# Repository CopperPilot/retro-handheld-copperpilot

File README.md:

# CopperPilot Retro Handheld: 4-Layer ESP32-S3 Handheld Console Hardware

The CopperPilot Retro Handheld is an ultra-compact, single-board retro handheld console design built on a 4-layer FR-4 PCB (**63.00 mm x 80.00 mm**) with a parametric snap-fit enclosure. Built around an Espressif ESP32-S3 dual-core microcontroller, the hardware features a 2.4-inch 320x240 ILI9341 SPI color TFT display, 14 responsive gameplay and shoulder pushbuttons, integrated USB-C charging and native USB-OTG/JTAG programming, automatic load-sharing battery power management for uninterrupted gameplay while charging, and a removable 1000 mAh Li-Po cell.

> **Project status:** this repository contains the hardware (schematic, PCB, enclosure CAD, and manufacturing outputs) only. There is **no firmware yet**, so no frame rates, emulator compatibility, or battery runtime have been measured on this board.

---

## 3D Enclosure & Industrial Design Showcase

### 3D CAD Enclosure Renders

| Front Face & Controls | Rear Shell & Grip Channels |
| :---: | :---: |
|  |  |
| **Front bezel, display window & keycaps** | **Rear grooved shell & battery hatch** |

| 3/4 Isometric View | Exploded Subsystem Assembly |
| :---: | :---: |
|  |  |
| **Assembled enclosure** | **Front Bezel, PCBA, Floating Keycaps, Rear Shell & Door** |

### Complete 3D Assembly Motion Animation (GIF & MP4)

<p align="center">
  
  <br>
  <em>Sequential 3D Assembly Animation: PCBA SMT/TH Component Populating &rarr; Gamepad Keycaps Seating over Tactile Switches &rarr; 2.4" Display Panel Seating &amp; FPC Interconnect into J3 &rarr; Front Bezel Lowering over Controls &amp; Alignment Pins &rarr; Li-Po Battery Seating into Rear Cavity &rarr; Rear Grooved Shell Closing &amp; Flush Snap Mating &rarr; 360&deg; Watertight Turntable Inspection</em>
  <br>
  <strong>High-definition MP4 video asset:</strong> <code>docs/images/case_assembly_video.mp4</code>
</p>

---

## 4-Layer Routed PCB Layout & Schematic Capture

| Front Layer (`F.Cu` — Tactile Controls & Display) | Back Layer (`B.Cu` — ESP32-S3, USB-C & Power ICs) |
| :---: | :---: |
|  |  |

### Photorealistic 3D KiCad PCB Renders (`kicad-cli pcb render`)

| KiCad 3D Top View (Tactile Controls, JST-GH J3 & Top Shoulder Switches) | KiCad 3D Bottom View (ESP32-S3 Module, USB-C, JST-PH & Power Management) |
| :---: | :---: |
|  |  |
| *Populated Front: 14x Tactile Switches, J3 Display Receptacle, D1/D3 LEDs* | *Populated Back: ESP32-S3-WROOM-1, USB-C, JST-PH Battery Header, LDO & Charger* |

<p align="center">
  
  <br>
  <em>Complete 6-Block Schematic Capture (USB-C Power, Li-Po Charger, Load Sharing, ESP32-S3 Core, ILI9341 TFT & 14 Pushbuttons)</em>
</p>

---

## System Architecture

```
                    +-------------------------------------------------------+
                    |                   Power Subsystem                     |
                    | USB-C (J1) ---> USBLC6-2SC6 (U1) ESD Protection       |
                    |                 |                                     |
                    |                 +---> MCP73831 (U2) Charger (500mA)   |
                    |                 |     |                               |
                    |                 |     v                               |
                    |                 |    JST-PH 1S LiPo (J2)              |
                    |                 |     |                               |
                    |                 v     v                               |
                    |           AO3401A (Q1) + MBR0520 (D2) Power Path      |
                    |                       | (Auto Load-Sharing)           |
                    |                       v                               |
                    |              Main Power Switch (SW1)                  |
                    |                       |                               |
                    |                       +---> 100k/100k Divider (IO1)   |
                    |                       v                               |
                    |              AP2112K-3.3 (U3) 600mA LDO               |
                    +-----------------------|-------------------------------+
                                            | +3.3V System Rail
+--------------------------+  Hardware FSPI +-------------------------------+
|  2.4" 320x240 ILI9341    |<---------------|       ESP32-S3-WROOM-1        |
|  SPI Color TFT (J3)      |  SCK, MOSI,    |  Dual-Core Xtensa LX7 240MHz  |
|  2N7002 Backlight Driver |<---------------|  512KB SRAM, 8MB Flash        |
+--------------------------+  CS, DC, RST,  |  2MB PSRAM, Wi-Fi 4 / BLE 5.0 |
                              PWM Backlight +---+---+---+---+---+---+---+---+
                                                |   |   |   |   |   |   |
     14x Active-Low Tactile Pushbuttons:        |   |   |   |   |   |   |
     D-Pad (Up, Down, Left, Right) <------------+   |   |   |   |   |   |
     Action Diamond (A, B, X, Y) <------------------+   |   |   |   |   |
     Utility Controls (Select, Start) <-----------------+   |   |   |   |
     Shoulder Triggers (L1, L2, R1, R2) <-------------------+   |   |   |
     Boot & Reset Service Switches (SW2, SW3) <-----------------+---+---+
```

---

## Hardware Specifications & Computational Capability

- **Chassis & Form Factor**: 63.00 mm x 80.00 mm ultra-compact 4-layer FR-4 PCB with R=2.50 mm corner radii, 4 precision 2.20 mm alignment holes (`H1`–`H4`), and 4 through-PCB snap-hook retention notches (`SL1`, `SL2`, `SR1`, `SR2`).
- **Core Processing Unit**: Espressif ESP32-S3-WROOM-1-N8R2 (dual-core 32-bit Xtensa LX7 @ 240 MHz, 512 KB internal SRAM, 8 MB Quad-SPI Flash, 2 MB Quad-SPI PSRAM, 2.4 GHz 802.11 b/g/n Wi-Fi + Bluetooth 5.0 LE).
  - **Game & Emulator Capability (not yet verified on this board)**: There is no firmware for this board yet, so no frame rates or emulator results are claimed here. The figures below are design-level estimates and third-party reports from other ESP32-S3 hardware, cited for reference only:
    - Display link: the ESP32-S3 SPI2 (FSPI) peripheral supports DMA transfers. A full 320x240 RGB565 frame is 150 KB (300 KB double-buffered, well within the 2 MB PSRAM). Achievable frame rate depends on the SPI clock the ILI9341 panel and cabling sustain in practice (commonly 40 MHz). The [esp-box-emu](https://github.com/esp-cpp/esp-box-emu) project reports a "~31 fps ceiling" for 320x240x16bpp output on its ESP32-S3 panel.
    - Emulators on other ESP32-S3 devices: [esp-box-emu](https://github.com/esp-cpp/esp-box-emu) runs NES (nofrendo), Game Boy / Game Boy Color (gnuboy), Sega Master System / Game Gear, Genesis and Doom on the ESP32-S3-BOX. [Retro-Go](https://github.com/ducalex/retro-go) supports NES, Game Boy / Color, Master System, Game Gear, PC Engine and more on ESP32 handhelds, with ESP32-S3 community ports. [PaperBoy S3](https://www.tomshardware.com/video-games/retro-gaming/designer-turns-niche-e-ink-dev-board-into-a-60hz-game-boy-handheld-960x540-display-powered-by-ultra-low-cost-esp32-s3-microcontroller) (Tom's Hardware) runs a Game Boy emulator on an ESP32-S3, with the chip fully loaded.
    - These results come from different hardware and firmware. Performance on this board has to be measured once firmware exists.
    - *Audio note*: The board does not integrate an analog audio amplifier or speaker. Audio is supported wirelessly via Bluetooth 5.0 LE / A2DP or via external PWM buzzer on spare GPIO.
- **Display Subsystem & Connector `J3`**:
  - **Board-Mounted SMT Socket (`J3`)**: JST Sales America `SM10B-GHS-TB(LF)(SN)` (10-position 1.25 mm pitch horizontal SMD header with solder retention tabs).
  - **Turnkey Sourced Display Module (`DISP1`)**: **Waveshare 15933** (MPN: `15933` / DigiKey: `2649-15933-ND` / LCSC: `C2913222`) or EastRising `ER-TFT024-3`.
    - 2.4-inch 320x240 RGB TFT LCD, Sitronix/Ilitek ILI9341 4-wire SPI controller, 3.3V DC logic, active area 48.96 x 36.72 mm, 10-conductor cable harness with mating plug JST `GHR-10V-S`.
  - Onboard 2N7002 N-channel MOSFET backlight switch (`Q2`) with 10 Ω ballast resistor (`R14`) and 100 kHz PWM brightness dimming on GPIO21.
- **Power Management & Dynamic Load-Sharing**:
  - Microchip MCP73831T-2ACI/OT linear Li-Po/Li-Ion charge management controller configured for 500 mA fast charge (`R_PROG` = 2.0 kΩ 1%).
  - Automatic dynamic load sharing via AO3401A P-channel MOSFET (`Q1`, $R_{DS(on)} < 50\text{ m}\Omega$) and MBR0520 Schottky barrier diode (`D2`, $V_F = 0.38\text{ V}$). When 5V USB-C is plugged in, the system runs directly off USB power while the battery charges undisturbed at its full C-rate; upon disconnect, the MOSFET transparently switches system load back to battery without voltage droop.
  - Diodes Inc. AP2112K-3.3 ultra-low-dropout 600 mA CMOS regulator with 250 mV dropout voltage, powering the console reliably down to 3.55 V battery cutoff.
  - Precision 100 kΩ / 100 kΩ 1% resistor divider (`R8`, `R9`) with 100 nF smoothing capacitor (`C6`) on ESP32-S3 `ADC1_CH0` (GPIO1) for fuel gauge battery telemetry.
  - Estimated system consumption (design estimate, not measured): ~220 mA @ 3.3V (~0.73W) with display backlight at 100% and CPU at 240 MHz, which would give roughly 4.5 hours from a 1000 mAh Li-Po cell.
- **Controls & Non-Colliding 3D Keycaps**:
  - 14 front-mounted tactile switches with 10 kΩ pull-up networks:
    - 4-way D-Pad (`UP`, `DOWN`, `LEFT`, `RIGHT`) centered at (14.65, 60.96 mm).
    - 4-button action diamond (`A`, `B`, `X`, `Y`) centered at (47.97, 61.75 mm).
    - 2 utility buttons (`SELECT`, `START`) centered at (31.24, 69.70 mm).
    - 4 shoulder triggers (`L1`, `L2`, `R1`, `R2`) centered at (9.50, 18.33, 53.50, 44.67 mm).
  - **Guaranteed Physical Clearances**:
    - D-Pad to Select button flange clearance: **1.49 mm** (zero collision).
    - ABXY adjacent button flange clearance: **>1.22 mm** between all neighboring pairs.
    - L1/L2 and R2/R1 shoulder trigger gap: **0.93 mm** inter-button clearance.
    - Keycap-to-bezel sliding clearance: **0.30 mm** radial clearance for friction-free actuation.

---

## Lion Circuits 4-Layer Manufacturing & PCBA Specifications

The hardware has been validated against Lion Circuits India turnkey PCBA design and procurement standards:

| Fabrication Parameter | Lion Circuits Standard Capability | Handheld Console Implementation | Design Margin |
| :--- | :--- | :--- | :--- |
| **Layer Count** | 4-Layer Multi-Layer FR-4 | **4 Layers** (`F.Cu`, `In1.Cu`, `In2.Cu`, `B.Cu`) | Standard |
| **Finished Thickness** | 1.6 mm nominal (+/- 10%) | **1.60 mm** | Exact Nominal |
| **Copper Weight** | 1.0 oz outer / 0.5 oz inner | **1.0 oz (35 µm) outer / 0.5 oz (17.5 µm) inner** | Standard |
| **Minimum Trace Width** | 6 mil (0.1524 mm) | **6 mil (0.1524 mm) min / 8 mil (0.20 mm) typ** | 100% Fab Compliant |
| **Minimum Trace Spacing** | 6 mil (0.1524 mm) | **6 mil (0.1524 mm) min / 8 mil (0.20 mm) typ** | 100% Fab Compliant |
| **Via Drill & Diameter** | 0.30 mm drill / 0.60 mm pad | **0.30 mm drill / 0.60 mm diameter** | Exact Standard Spec |
| **Annular Ring** | 6 mil (0.152 mm) minimum | **0.150 mm (6 mil)** | 100% Fab Compliant |
| **Copper to Board Edge** | 12 mil (0.30 mm) minimum | **0.40 mm (16 mil)** | +33% Safety Margin |
| **Surface Finish** | Lead-Free HASL or ENIG | **Electroless Nickel Immersion Gold (ENIG)** | Superior SMT Coplanarity |
| **Solder Mask & Silk** | Matte Black Mask / White Silk | **Matte Black / High-Contrast White** | Premium Aesthetic |

### Turnkey PCBA Bill of Materials (45 Verified Line Items)

| Item | Designators | Qty | Part / Value | Manufacturer | MPN | Package | Sourcing Channel |
| :---: | :--- | :---: | :--- | :--- | :--- | :--- | :--- |
| 1 | `U4` | 1 | Dual-Core MCU + PSRAM | Espressif Systems | `ESP32-S3-WROOM-1-N8R2` | SMD-41 (18x25.5mm) | DigiKey / Mouser / LCSC |
| 2 | `J1` | 1 | USB-C 2.0 16-Pin Receptacle | GCT / Hroparts | `USB4105-GF-A` / `TYPE-C-31-M-12` | USB-C-16P-TopMount | DigiKey / LCSC |
| 3 | `U1` | 1 | Rail-to-Rail ESD Diode Array | STMicroelectronics | `USBLC6-2SC6` | SOT-23-6 | DigiKey / Mouser |
| 4 | `U2` | 1 | 500mA Li-Po Charger | Microchip Technology | `MCP73831T-2ACI/OT` | SOT-23-5 | DigiKey / Mouser |
| 5 | `Q1` | 1 | P-MOSFET Load Sharing | Alpha & Omega Semi | `AO3401A` | SOT-23 | DigiKey / LCSC |
| 6 | `D2` | 1 | 20V 0.5A Schottky Diode | ON Semiconductor | `MBR0520LT1G` | SOD-123 | DigiKey / Mouser |
| 7 | `U3` | 1 | 600mA Ultra-Low-Dropout LDO | Diodes Incorporated | `AP2112K-3.3TRG1` | SOT-23-5 | DigiKey / Mouser |
| 8 | `Q2` | 1 | 60V 300mA N-MOSFET Backlight | Nexperia | `2N7002,215` | SOT-23 | DigiKey / Mouser |
| 9 | `D1` | 1 | Red LED (Charge Indicator) | Lite-On Inc. | `LTST-C190KRKT` | 0603 SMD | DigiKey / Mouser |
| 10 | `D3` | 1 | Green LED (Power Good) | Lite-On Inc. | `LTST-C190KGKT` | 0603 SMD | DigiKey / Mouser |
| 11 | `J2` | 1 | JST-PH 2-Pin Battery Header | JST Sales America | `S2B-PH-K-S(LF)(SN)` | JST_PH_1x02_P2.00mm | DigiKey / Mouser |
| 12 | `J3` | 1 | JST-GH 10-Pin Display Socket | JST Sales America | `SM10B-GHS-TB(LF)(SN)` | 10-Pin 1.25mm SMT | DigiKey / Mouser |
| 13 | `SW1` | 1 | SPDT Power Slide Switch | C&K / Hroparts | `PCM12SMTR` / `MSK-12C02` | SMT Slide Switch | DigiKey / LCSC |
| 14 | `SW4`-`SW11` | 8 | 6x6mm Tactile Switches | C&K Components | `PTS645SM43SMTR92 LFS` | 6.0x6.0mm SMD | DigiKey / Mouser |
| 15 | `SW12`,`SW13`,`SW2`,`SW3` | 4 | 6x3.5mm Tactile Switches | C&K Components | `PTS636 SM25 LFS` | 6.0x3.5mm SMD | DigiKey / Mouser |
| 16 | `SW14`-`SW17` | 4 | Ultra-Small Tactile Switches | Omron Electronics | `B3U-3000P` | 3.0x2.5mm SMD | DigiKey / Mouser |
| 17 | `DISP1` | 1 | 2.4" 320x240 ILI9341 SPI TFT | Waveshare / EastRising | `15933` / `ER-TFT024-3` | 2.4" Module + Cable | DigiKey / LCSC / Waveshare |
| 18 | `BT1` | 1 | 3.7V 1000mAh 1S Li-Po Cell | PKCELL / Adafruit | `LP803040` / `ID 258` | 40x30x8.0mm JST-PH | DigiKey / Adafruit |
| 19 | `CASE1` | 1 | CopperPilot Retro Handheld 3D Snap-Fit Case Kit | CopperPilot (in-house design) | `CP-RETRO-HANDHELD-CASE-V1` | 3D Watertight Enclosure | 3D Printed / Molded |
| 20-34 | `C1`-`C15` | 15 | Ceramic MLCC Decoupling | Yageo / Murata | 100nF, 1uF, 4.7uF, 10uF, 22uF | 0603 & 0805 | DigiKey / LCSC |
| 35-45 | `R1`-`R30` | 30 | Precision Chip Resistors | Yageo / Vishay | 10, 22, 1k, 2k 1%, 5.1k, 10k, 100k 1% | 0603 & 0805 | DigiKey / LCSC |

---

## Automated Verification Suite

The repository includes a **51-point automated PyTest hardware, assembly, and enclosure verification suite**:

```bash
$ make test
============================= test session starts ==============================
platform linux -- Python 3.13.9, pytest-9.1.1
collected 51 items

tests/test_assembly_e2e.py::TestEndToEndAssemblySequence::test_stage1_pcba_component_loading PASSED
tests/test_assembly_e2e.py::TestEndToEndAssemblySequence::test_stage2_kicad_3d_pcba_mesh_validation PASSED
tests/test_assembly_e2e.py::TestEndToEndAssemblySequence::test_stage3_buttons_clearance_and_zero_collision PASSED
tests/test_assembly_e2e.py::TestEndToEndAssemblySequence::test_stage4_buttons_seat_onto_pcba_zero_collision PASSED
tests/test_assembly_e2e.py::TestEndToEndAssemblySequence::test_stage5_buttons_seat_in_front_bezel_zero_collision PASSED
tests/test_assembly_e2e.py::TestEndToEndAssemblySequence::test_stage6_display_shelf_mating_and_j3_interconnect PASSED
tests/test_assembly_e2e.py::TestEndToEndAssemblySequence::test_stage7_pcba_mating_to_front_bezel_zero_collision PASSED
tests/test_assembly_e2e.py::TestEndToEndAssemblySequence::test_stage8_rear_shell_mating_over_pcb_zero_collision PASSED
tests/test_assembly_e2e.py::TestEndToEndAssemblySequence::test_stage9_battery_seating_and_rear_cavity_fit PASSED
tests/test_assembly_e2e.py::TestEndToEndAssemblySequence::test_stage10_continuous_kinematic_assembly_trajectories PASSED
tests/test_assembly_e2e.py::TestEndToEndAssemblySequence::test_stage11_full_console_assembly_envelope PASSED
tests/test_case.py::TestCaseFiles::test_stl_file_exists[case_front_bezel.stl] PASSED
tests/test_case.py::TestCaseFiles::test_stl_file_exists[case_rear_grooved.stl] PASSED
tests/test_case.py::TestCaseFiles::test_stl_file_exists[case_battery_door.stl] PASSED
tests/test_case.py::TestCaseFiles::test_stl_file_exists[buttons_dpad_abxy_sest_shoulders.stl] PASSED
tests/test_case.py::TestCaseFiles::test_stl_file_exists[copperpilot_retro_handheld_assembly.stl] PASSED
tests/test_case.py::TestCaseGeometry::test_front_bezel_envelope PASSED
tests/test_case.py::TestCaseGeometry::test_rear_shell_envelope PASSED
tests/test_case.py::TestCaseGeometry::test_battery_door_envelope PASSED
tests/test_case.py::TestCaseGeometry::test_mesh_manifolds_and_faces PASSED
tests/test_case.py::TestCaseGeometry::test_full_assembly_mesh PASSED
tests/test_case.py::TestCaseClearancesAndCollisions::test_all_buttons_zero_collision PASSED
tests/test_case.py::TestCaseClearancesAndCollisions::test_abxy_adjacent_flange_clearances PASSED
tests/test_case.py::TestCaseClearancesAndCollisions::test_dpad_to_select_clearance PASSED
tests/test_case.py::TestCaseClearancesAndCollisions::test_shoulder_buttons_clearance PASSED
tests/test_case.py::TestCaseClearancesAndCollisions::test_snap_fit_engagement_and_boss_alignment PASSED
tests/test_pcb.py::TestBoardPhysical::test_board_dimensions PASSED
tests/test_pcb.py::TestBoardPhysical::test_four_layer_stackup PASSED
tests/test_pcb.py::TestBoardPhysical::test_edge_cuts_closed_contour PASSED
tests/test_pcb.py::TestConnectivityAndNetlist::test_drc_zero_unconnected_items PASSED
tests/test_pcb.py::TestConnectivityAndNetlist::test_drc_zero_errors PASSED
tests/test_pcb.py::TestConnectivityAndNetlist::test_erc_zero_errors PASSED
tests/test_pcb.py::TestConnectivityAndNetlist::test_all_critical_nets_present PASSED
tests/test_pcb.py::TestConnectivityAndNetlist::test_no_dangling_track_stubs PASSED
tests/test_pcb.py::TestConnectivityAndNetlist::test_no_unassigned_vias PASSED
tests/test_pcb.py::TestTraceGeometryAndDFM::test_signal_trace_min_width PASSED
tests/test_pcb.py::TestTraceGeometryAndDFM::test_power_rail_trace_widths PASSED
tests/test_pcb.py::TestTraceGeometryAndDFM::test_via_drill_and_annular_ring PASSED
tests/test_pcb.py::TestTraceGeometryAndDFM::test_zero_clearance_errors PASSED
tests/test_pcb.py::TestSubsystemsAndComponents::test_mcu_esp32s3_placement PASSED
tests/test_pcb.py::TestSubsystemsAndComponents::test_usb_c_and_esd_protection PASSED
tests/test_pcb.py::TestSubsystemsAndComponents::test_power_management_and_charger PASSED
tests/test_pcb.py::TestSubsystemsAndComponents::test_power_path_and_regulator PASSED
tests/test_pcb.py::TestSubsystemsAndComponents::test_display_connector_on_front PASSED
tests/test_pcb.py::TestSubsystemsAndComponents::test_all_14_front_tactile_switches PASSED
tests/test_pcb.py::TestSubsystemsAndComponents::test_boot_and_reset_tactile_switches PASSED
tests/test_pcb.py::TestGroundPlanesAndZoning::test_ground_planes_exist PASSED
tests/test_pcb.py::TestGroundPlanesAndZoning::test_ground_via_density PASSED
tests/test_pcb.py::Test3DModelsAndSilkscreen::test_all_footprints_have_3d_models PASSED
tests/test_pcb.py::Test3DModelsAndSilkscreen::test_no_legacy_kicad_env_vars PASSED
tests/test_pcb.py::Test3DModelsAndSilkscreen::test_pin1_polarity_indicators PASSED

============================== 51 passed ==============================
```

---

## Repository Structure

```
.
├── Makefile                            # Top-level orchestrator (test, drc, erc, fab, gerbers)
├── .gitignore                          # Comprehensive Git exclusion rules
├── LICENSE                             # CERN Open Hardware Licence v2 - Permissive
├── README.md                           # Master hardware, pinout, and manufacturing documentation
├── export_manufacturing.py             # Lion Circuits release generator (Gerbers, CPL, BOM, D356)
├── copperpilot-retro-handheld.kicad_pro       # KiCad 10 project definition & netclass rules
├── copperpilot-retro-handheld.kicad_sch       # Hierarchical schematic capture (0 ERC errors)
├── copperpilot-retro-handheld.kicad_pcb       # 4-layer PCB layout (100% routed, 0 DRC violations)
├── sym-lib-table                       # Symbol library mapping
├── fp-lib-table                        # Footprint library mapping
├── libs/                               # Custom symbols and footprints
│   ├── copperpilot_retro_handheld.kicad_sym      # Custom ILI9341 2.4" TFT display symbol
│   └── copperpilot_retro_handheld.pretty/        # Custom 10-pin display footprint & 3D model
├── tests/                              # Automated 51-point hardware & assembly verification suite
│   ├── conftest.py                     # S-expression AST parsers & KiCad CLI fixtures
│   ├── test_assembly_e2e.py            # 11-stage end-to-end mechanical assembly verification
│   ├── test_pcb.py                     # 25-point PCB geometry, connectivity, DFM & circuit tests
│   └── test_case.py                    # 15-point 3D mechanical enclosure & clearance tests
├── case/                               # Parametric 3D snap-fit enclosure CAD subsystem
│   ├── Makefile                        # Targets: generate, render, test, clean
│   ├── README.md                       # Enclosure mechanics, snap-fit physics & 3D print specs
│   ├── generate_case.py                # Parametric CSG mesh synthesis in Trimesh & Manifold3D
│   ├── render_case.py                  # High-resolution PyVista rendering & animation engine
│   ├── models/                         # Watertight production-ready STL models
│   │   ├── case_front_bezel.stl        # Front bezel with screen window & non-colliding bores
│   │   ├── case_rear_grooved.stl       # Rear shell with 14 grip channels & snap catch pockets
│   │   ├── case_battery_door.stl       # Removable battery bay hatch with retention lip
│   │   ├── buttons_dpad_abxy_*.stl     # Complete set of floating button keycaps (>1.2mm gap)
│   │   └── copperpilot_retro_handheld_assembly.stl # Full mated console assembly
│   └── renders/                        # Multi-view isometric, front, rear, and exploded renders
└── docs/
    └── images/                         # Documentation renders and animations
        ├── case_render_*.png           # Front, rear, isometric & exploded CAD renders
        ├── case_explosion_animation.gif# 64-frame 3D sequential assembly motion animation
        └── case_assembly_video.mp4     # High-definition MP4 assembly video asset
```

---

## Quickstart & Manufacturing Commands

Ensure `kicad-cli` (v10.0+) and Python 3.10+ (with `uv`) are available in your path:

### 1. Run Automated Verification & Rule Checks
```bash
# Run full 51-point PyTest verification suite (installs test deps via uv)
make test

# Run electrical rule check (ERC) via KiCad CLI
kicad-cli sch erc copperpilot-retro-handheld.kicad_sch

# Run design rule check (DRC) via KiCad CLI
kicad-cli pcb drc copperpilot-retro-handheld.kicad_pcb
```

### 2. Generate 3D CAD Enclosure STLs and Visuals
```bash
# Generate watertight STL models
make build-case

# Render smooth anti-aliased images and assembly animation
make render-case
```

### 3. Generate Turnkey Manufacturing Release Bundle
```bash
# Generate gerbers, drill, CPL, structured BOM, and release zip
make fab
```

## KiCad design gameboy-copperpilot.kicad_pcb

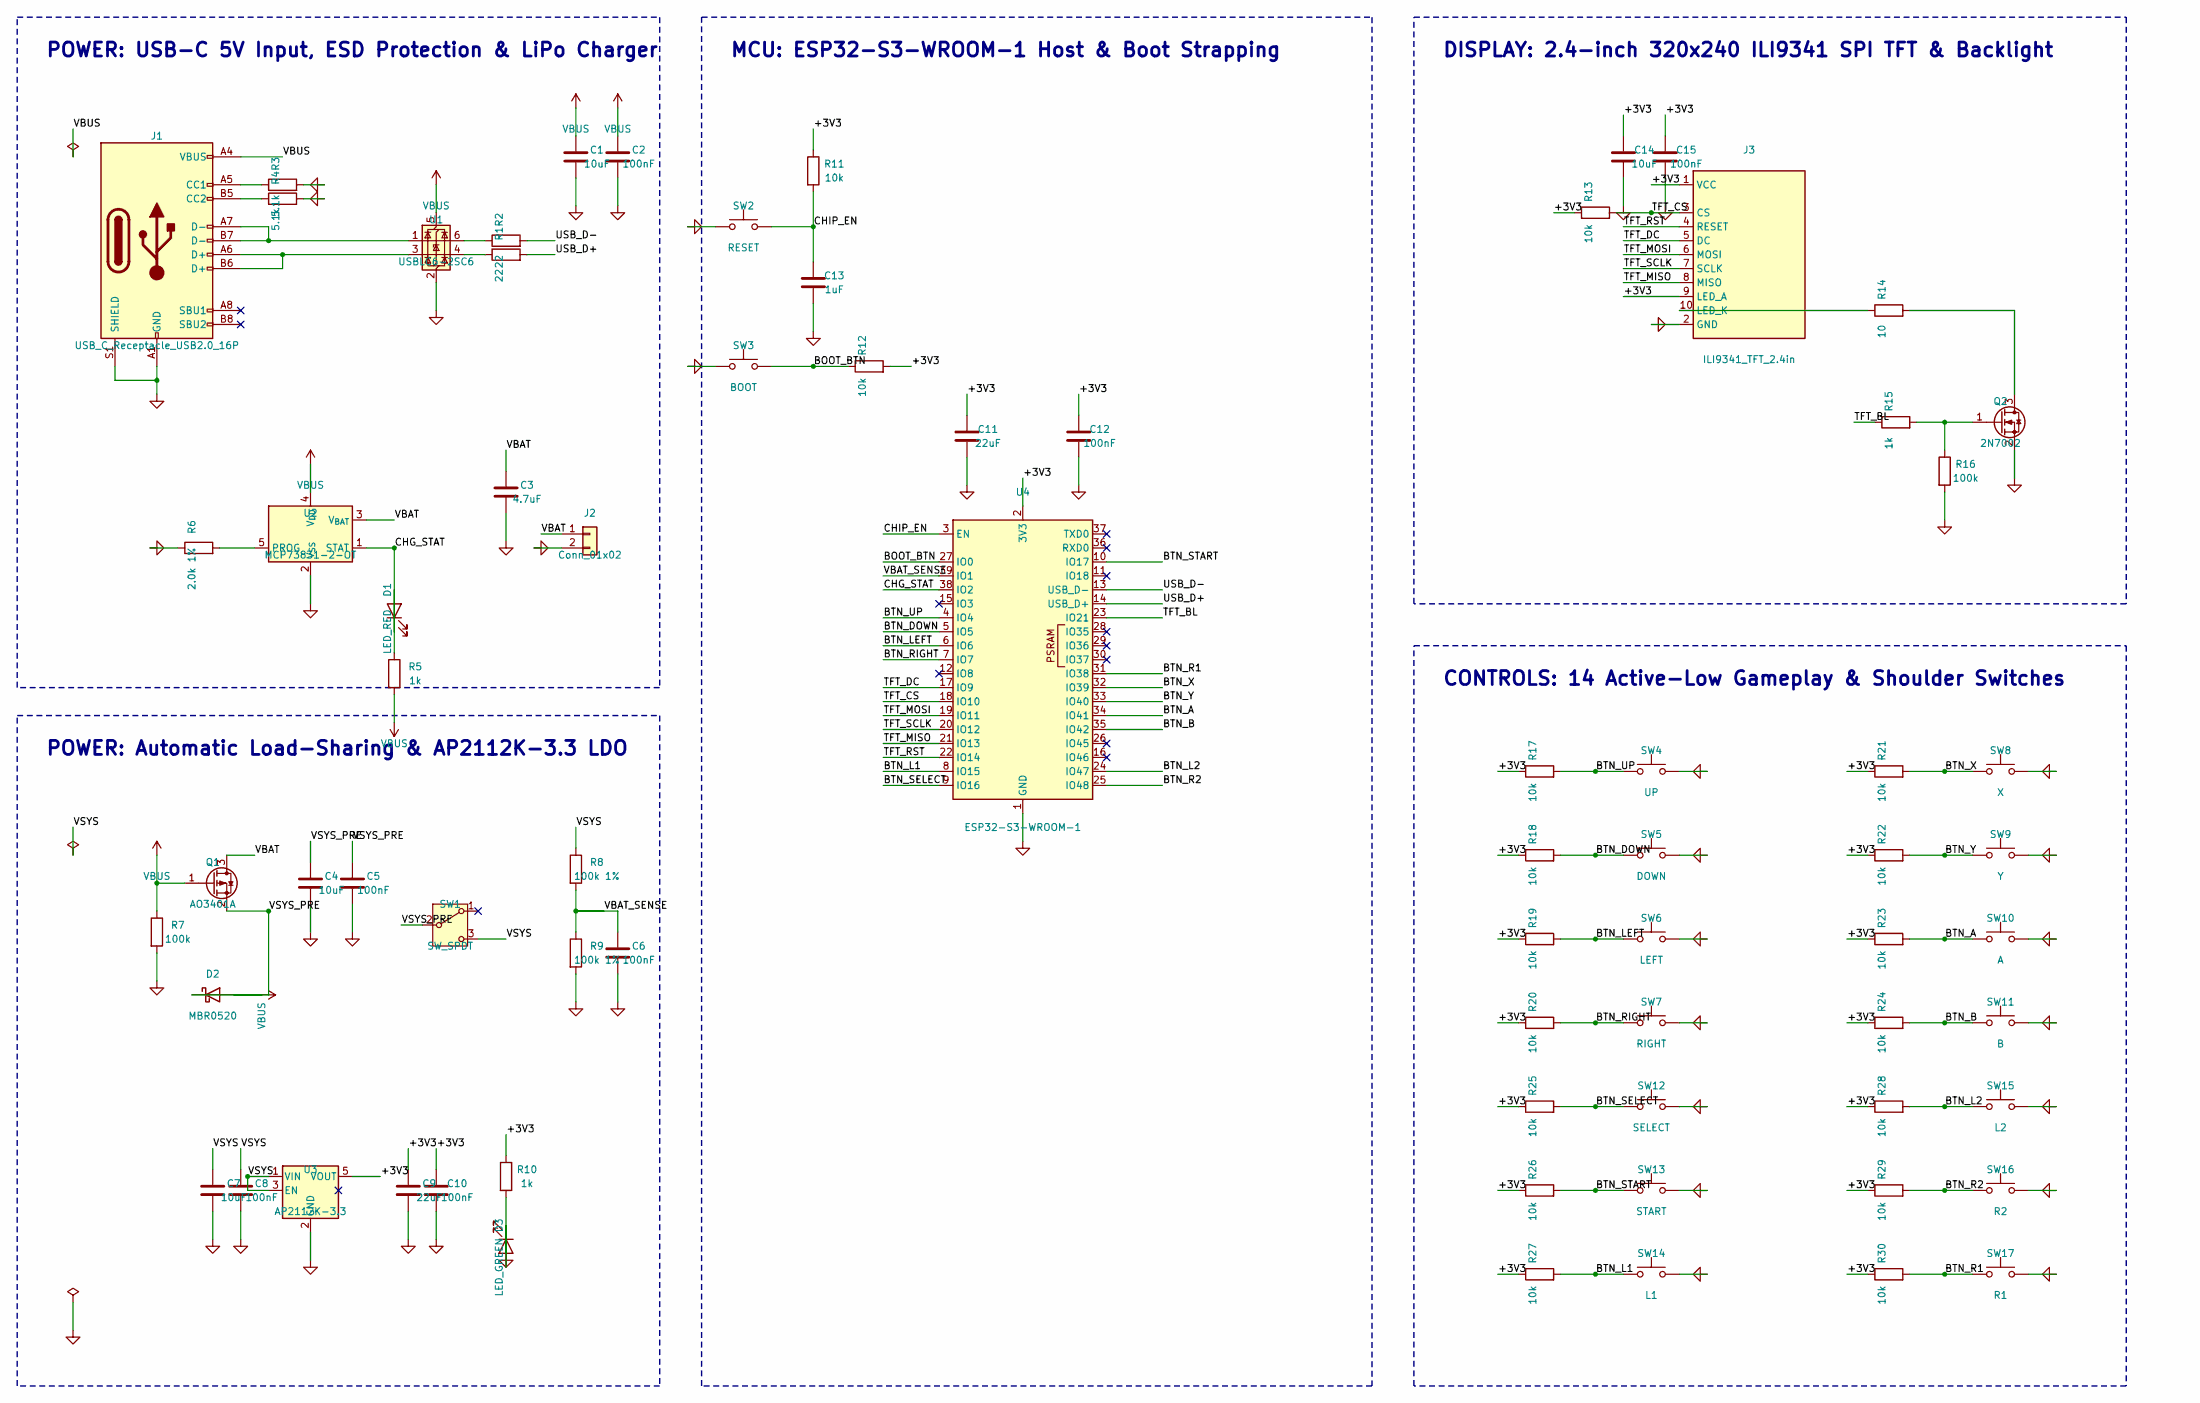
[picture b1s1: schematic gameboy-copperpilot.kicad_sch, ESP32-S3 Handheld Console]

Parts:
C1, C4, C7, C14: 10uF; C_0805_2012Metric
C2, C5, C6, C8, C10, C12, C15: 100nF; C_0603_1608Metric
C3: 4.7uF; C_0603_1608Metric
C9, C11: 22uF; C_0805_2012Metric
C13: 1uF; C_0603_1608Metric
D1: LED_RED; LED_0603_1608Metric
D2: MBR0520; D_SOD-123
D3: LED_GREEN; LED_0603_1608Metric
J1: USB_C_Receptacle_USB2.0_16P; USB_C_Receptacle_GCT_USB4105-xx-A_16P_TopMnt_Horizontal
J2: Conn_01x02; JST_PH_S2B-PH-K_1x02_P2.00mm_Horizontal
J3: ILI9341_TFT_2.4in; ILI9341_TFT_2.4in_10P
Q1: AO3401A; SOT-23
Q2: 2N7002; SOT-23
R1, R2: 22; R_0603_1608Metric
R3, R4: 5.1k; R_0603_1608Metric
R5, R10, R15: 1k; R_0603_1608Metric
R6: 2.0k 1%; R_0603_1608Metric
R7, R16: 100k; R_0603_1608Metric
R8, R9: 100k 1%; R_0603_1608Metric
R11, R12, R13, R17, R18, R19, R20, R21, R22, R23, R24, R25, R26, R27, R28, R29, R30: 10k; R_0603_1608Metric
R14: 10; R_0805_2012Metric
SW1: SW_SPDT; SW_SPDT_PCM12
SW2: RESET; SW_Tactile_SPST_NO_Straight_CK_PTS636Sx25SMTRLFS
SW3: BOOT; SW_Tactile_SPST_NO_Straight_CK_PTS636Sx25SMTRLFS
SW4: UP; SW_SPST_PTS645Sx43SMTR92
SW5: DOWN; SW_SPST_PTS645Sx43SMTR92
SW6: LEFT; SW_SPST_PTS645Sx43SMTR92
SW7: RIGHT; SW_SPST_PTS645Sx43SMTR92
SW8: X; SW_SPST_PTS645Sx43SMTR92
SW9: Y; SW_SPST_PTS645Sx43SMTR92
SW10: A; SW_SPST_PTS645Sx43SMTR92
SW11: B; SW_SPST_PTS645Sx43SMTR92
SW12: SELECT; SW_Tactile_SPST_NO_Straight_CK_PTS636Sx25SMTRLFS
SW13: START; SW_Tactile_SPST_NO_Straight_CK_PTS636Sx25SMTRLFS
SW14: L1; SW_SPST_B3U-3000P
SW15: L2; SW_SPST_B3U-3000P
SW16: R2; SW_SPST_B3U-3000P
SW17: R1; SW_SPST_B3U-3000P
U1: USBLC6-2SC6; SOT-23-6
U2: MCP73831-2-OT; SOT-23-5
U3: AP2112K-3.3; SOT-23-5
U4: ESP32-S3-WROOM-1

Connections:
/+3V3: C9.1, C10.1, C11.1, C12.1, C14.1, C15.1, J3.1 (VCC), J3.9 (LED_A), R10.1, R11.1, R12.2, R13.1, R17.1, R18.1, R19.1, R20.1, R21.1, R22.1, R23.1, R24.1, R25.1, R26.1, R27.1, R28.1, R29.1, R30.1, U3.5 (VOUT), U4.2 (3V3)
/BOOT_BTN: R12.1, SW3.2, U4.27 (IO0)
/BTN_A: R23.2, SW10.1, U4.34 (IO41)
/BTN_B: R24.2, SW11.1, U4.35 (IO42)
/BTN_DOWN: R18.2, SW5.1, U4.5 (IO5)
/BTN_L1: R27.2, SW14.1, U4.8 (IO15)
/BTN_L2: R28.2, SW15.1, U4.24 (IO47)
/BTN_LEFT: R19.2, SW6.1, U4.6 (IO6)
/BTN_R1: R30.2, SW17.1, U4.31 (IO38)
/BTN_R2: R29.2, SW16.1, U4.25 (IO48)
/BTN_RIGHT: R20.2, SW7.1, U4.7 (IO7)
/BTN_SELECT: R25.2, SW12.1, U4.9 (IO16)
/BTN_START: R26.2, SW13.1, U4.10 (IO17)
/BTN_UP: R17.2, SW4.1, U4.4 (IO4)
/BTN_X: R21.2, SW8.1, U4.32 (IO39)
/BTN_Y: R22.2, SW9.1, U4.33 (IO40)
/CHG_STAT: D1.1 (K), U2.1 (STAT), U4.38 (IO2)
/CHIP_EN: C13.1, R11.2, SW2.2, U4.3 (EN)
/TFT_BL: R15.1, U4.23 (IO21)
/TFT_CS: J3.3 (CS), R13.2, U4.18 (IO10)
/TFT_DC: J3.5 (DC), U4.17 (IO9)
/TFT_MISO: J3.8 (MISO), U4.21 (IO13)
/TFT_MOSI: J3.6 (MOSI), U4.19 (IO11)
/TFT_RST: J3.4 (RESET), U4.22 (IO14)
/TFT_SCLK: J3.7 (SCLK), U4.20 (IO12)
/USB_D+: R1.2, U4.14 (USB_D+)
/USB_D-: R2.2, U4.13 (USB_D-)
/VBAT: C3.1, J2.1, Q1.3 (D), U2.3 (V_{BAT})
/VBAT_SENSE: C6.1, R8.2, R9.1, U4.39 (IO1)
/VSYS: C7.1, C8.1, R8.1, SW1.3 (C), U3.1 (VIN), U3.3 (EN)
unnamed: D1.2 (A), R5.1
unnamed: J1.A5 (CC1), R3.1
unnamed: J1.B5 (CC2), R4.1
unnamed: J1.A6 (D+), J1.B6 (D+), U1.3 (I/O2)
unnamed: J1.A7 (D-), J1.B7 (D-), U1.1 (I/O1)
unnamed: J3.10 (LED_K), R14.1
unnamed: Q2.3 (D), R14.2
unnamed: Q2.1 (G), R15.2, R16.1
unnamed: R1.1, U1.4 (I/O2)
unnamed: R2.1, U1.6 (I/O1)
unnamed: R6.2, U2.5 (PROG)

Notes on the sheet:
POWER: USB-C 5V Input, ESD Protection & LiPo Charger
POWER: Automatic Load-Sharing & AP2112K-3.3 LDO
MCU: ESP32-S3-WROOM-1 Host & Boot Strapping
DISPLAY: 2.4-inch 320x240 ILI9341 SPI TFT & Backlight
CONTROLS: 14 Active-Low Gameplay & Shoulder Switches

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
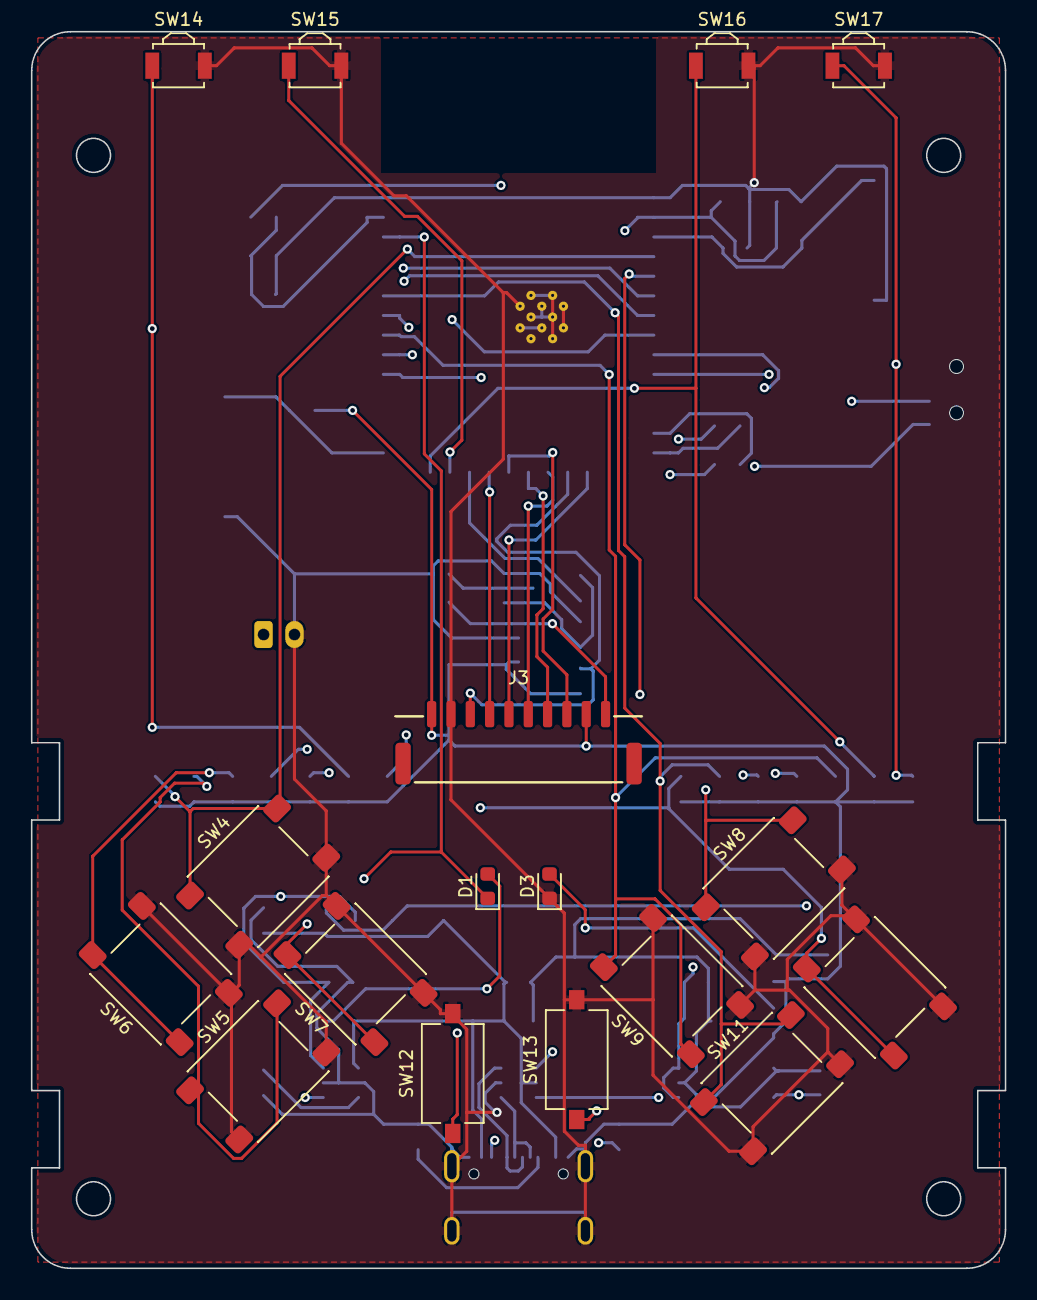
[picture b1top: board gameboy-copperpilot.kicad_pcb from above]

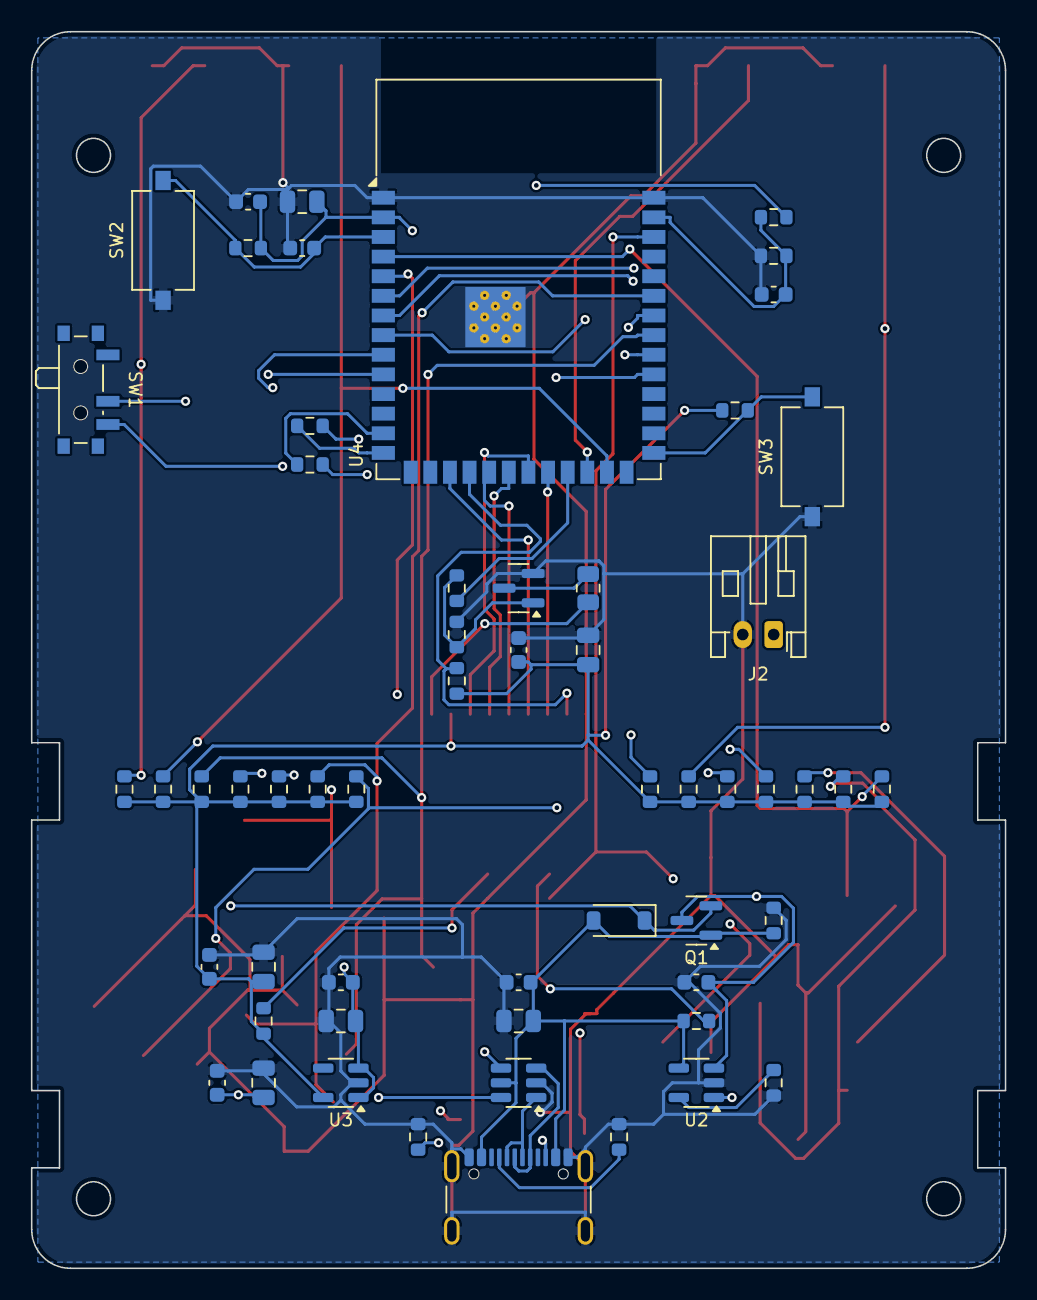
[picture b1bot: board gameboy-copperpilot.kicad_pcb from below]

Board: 4 copper layers, 63.0 x 80.0 mm, 74 parts (57 on the bottom side), 45 nets.
